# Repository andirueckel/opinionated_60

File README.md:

# opinionated_60

The opinionated_60 is a fixed-layout ANSI-based 60% mechanical keyboard PCB for *Cherry MX*-style switches with split `BACKSPACE`, split `RIGHT_SHIFT`, and 7u `SPACE` bar; there’s **no** option for a stepped `CAPS_LOCK` key.

The opinionated_60 is a rather modified, stripped-down, cleaned-up, and re-wired revision of the [Plain60 MKD Edition](https://github.com/manzel/plain60-mkd-edition) (ANSI version) by [manzel](https://github.com/manzel), which itself is a modified version of the [Plain60 Flex Edition](https://github.com/evyd13/plain60-flex-edition) (rev2.2) by [evyd13](https://github.com/evyd13).

The PCB design and schematics were created in [KiCad 8.0.2](https://www.kicad.org/blog/2024/04/KiCad-8.0.2-Release/).

## Features

  - Fits the SINGAKBD × TGR Unikorn and the HAYTCO CAKE60! <3
  - QMK and Vial support via the respective [firmware](/firmware)
  - No LEDs, no RGB, and no underglow!
  - *n*-key rollover (NKRO)

Also fits most universal 60% cases (Mekanisk Klippe & Fjell, KBDfans Tofu, etc.), where *fits* means *Unikorn*-style *gummy o-ring friction fit*, not traditional *tray mount* as there’s **no** holes for screws! Consider universal 60% case support experimental, and please do your research regarding your specific (use) case.

## Specifications

  - ATmega32U4-AU microcontroller
  - USB 2.0 Type-C connector *(default)*, and/or
  - JST connector for unified daughterboard *(optional)*
  - ESD protection chip and fuse to protect the PCB
  - ISP pin holes for flashing [QMK](https://github.com/qmk/qmk_firmware) and [Vial](https://github.com/vial-kb/vial-qmk) firmware
  - AST1109MLTRQ audio indicator (piezo buzzer/speaker) *(optional)*

## Layout

The 7u bottom row can be configured as *blockerless*, *WKL (winkeyless)*, or *HHKB*-style.

## Plate

The plate drawings were created in KiCad’s PCB design tool and could be manufactured as “PCB” from e.g. aluminum base material or regular FR-4 in any color. CNC-machining the plate has not been attempted, yet.

## Production

PCB and plate production files for can be found in the [Gerber](/hardware/Gerber) directory.

The production files were generated via [JLCKicadTools](https://github.com/matthewlai/JLCKicadTools).

## DISCLAIMER

Absolutely no guarantee for anything.

Use at your own risk!

## LICENSE

Creative Commons Attribution Share Alike 4.0 International (CC-BY-SA-4.0)

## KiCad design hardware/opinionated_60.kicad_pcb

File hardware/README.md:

# opinionated_60

The [opinionated_60](/) is a fixed-layout ANSI-based 60% mechanical keyboard PCB for *Cherry MX*-style switches with split `BACKSPACE`, split `RIGHT_SHIFT`, and 7u `SPACE` bar; there’s **no** option for a stepped `CAPS_LOCK` key.

The opinionated_60 is a rather modified, stripped-down, cleaned-up, and re-wired revision of the [Plain60 MKD Edition](https://github.com/manzel/plain60-mkd-edition) (ANSI version) by [manzel](https://github.com/manzel), which itself is a modified version of the [Plain60 Flex Edition](https://github.com/evyd13/plain60-flex-edition) (rev2.2) by [evyd13](https://github.com/evyd13).

The PCB design and schematics were created in [KiCad 8.0.2](https://www.kicad.org/blog/2024/04/KiCad-8.0.2-Release/).

## Features

  - Fits the SINGAKBD × TGR Unikorn and the HAYTCO CAKE60! <3
  - QMK and Vial support via the respective [firmware](/firmware)
  - No LEDs, no RGB, and no underglow!
  - *n*-key rollover (NKRO)

Also fits most universal 60% cases (Mekanisk Klippe & Fjell, KBDfans Tofu, etc.), where *fits* means *Unikorn*-style *gummy o-ring friction fit*, not traditional *tray mount* as there’s **no** holes for screws! Consider universal 60% case support experimental, and please do your research regarding your specific (use) case.

## Specifications

  - ATmega32U4-AU microcontroller
  - USB 2.0 Type-C connector *(default)*, and/or
  - JST connector for unified daughterboard *(optional)*
  - ESD protection chip and fuse to protect the PCB
  - ISP pin holes for flashing [QMK](https://github.com/qmk/qmk_firmware) and [Vial](https://github.com/vial-kb/vial-qmk) firmware
  - AST1109MLTRQ audio indicator (piezo buzzer/speaker) *(optional)*

## Layout

The 7u bottom row can be configured as *blockerless*, *WKL (winkeyless)*, or *HHKB*-style.

## Plate

The plate drawings were created in KiCad’s PCB design tool and could be manufactured as “PCB” from e.g. aluminum base material or regular FR-4 in any color. CNC-machining the plate has not been attempted, yet.

## Production

PCB and plate production files for can be found in the [Gerber](/hardware/Gerber) directory.

The production files were generated via [JLCKicadTools](https://github.com/matthewlai/JLCKicadTools).

## DISCLAIMER

Absolutely no guarantee for anything.

Use at your own risk!

## LICENSE

Creative Commons Attribution Share Alike 4.0 International (CC-BY-SA-4.0)

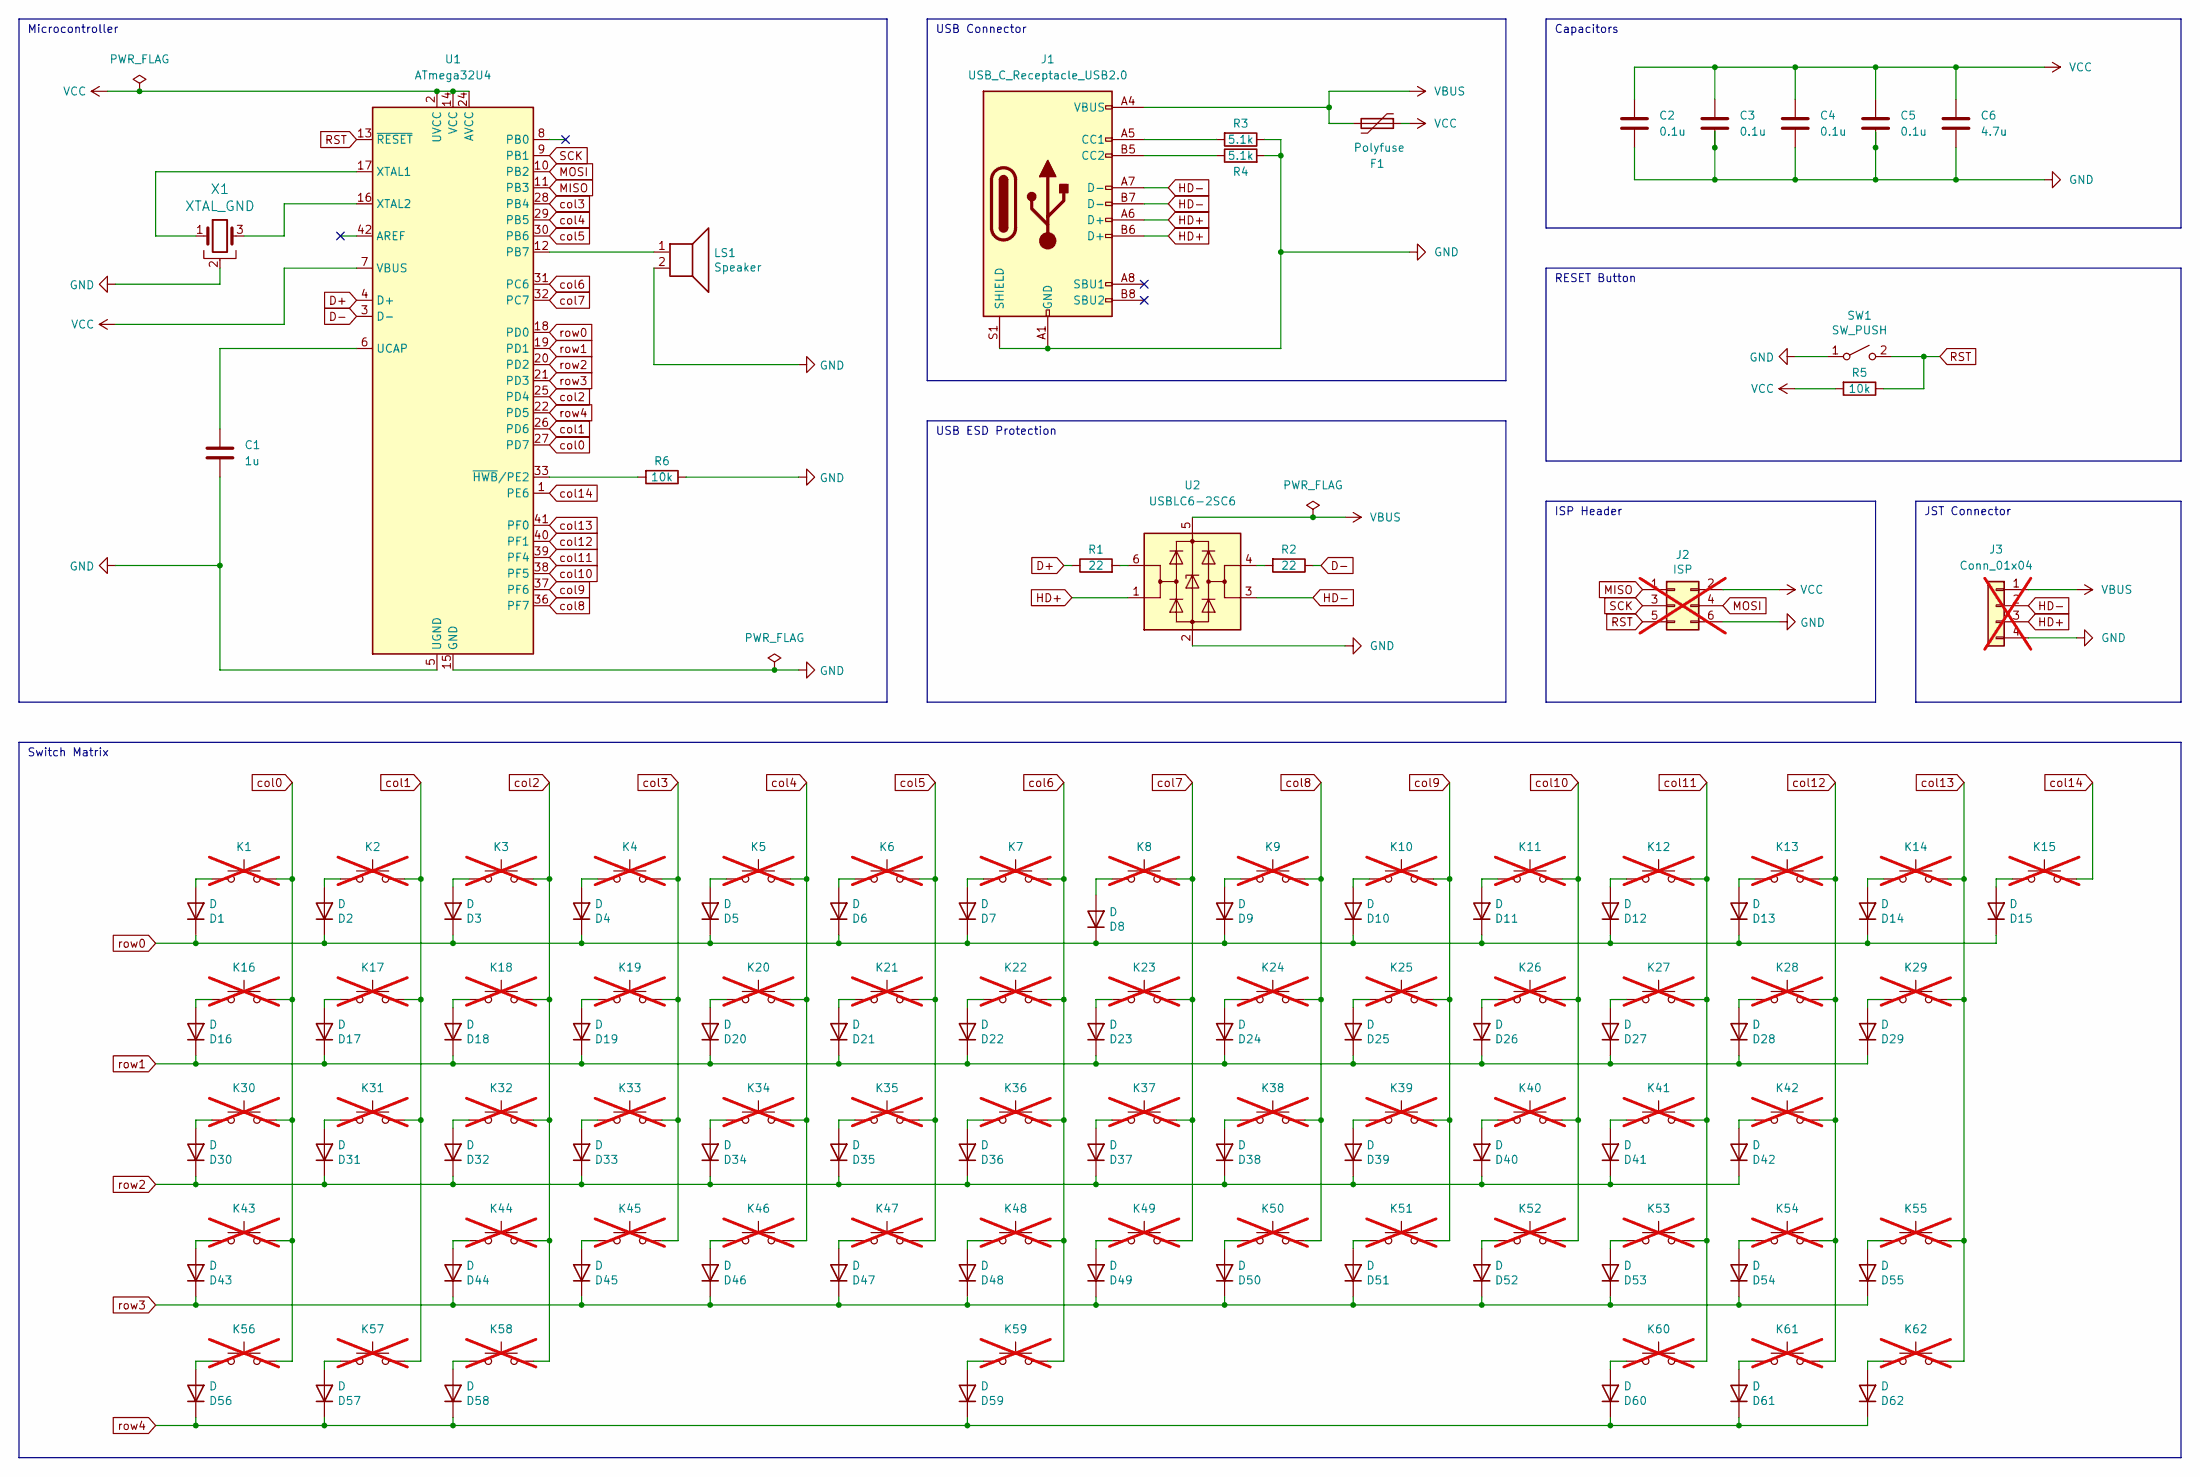
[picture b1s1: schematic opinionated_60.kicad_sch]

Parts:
C1: 1u; C_0805_2012Metric; LCSC part number C28323
C2, C3, C4, C5: 0.1u; C_0805_2012Metric; LCSC part number C49678
C6: 4.7u; C_0805_2012Metric; LCSC part number C1779
D1, D2, D3, D4, D5, D6, D7, D8, D9, D10, D11, D12, D13, D14, D15, D16, D17, D18, D19, D20, D21, D22, D23, D24, D25, D26, D27, D28, D29, D30, D31, D32, D33, D34, D35, D36, D37, D38, D39, D40, D41, D42, D43, D44, D45, D46, D47, D48, D49, D50, D51, D52, D53, D54, D55, D56, D57, D58, D59, D60, D61, D62: D; D_SOD-123; LCSC part number C2099
F1: Polyfuse; Fuse_0805_2012Metric; LCSC part number C261942
J1: USB_C_Receptacle_USB2.0; USB_C_Receptacle_HRO_TYPE-C-31-M-12; LCSC part number C165948
J2: ISP; PinHeader_2x03_P2.54mm_Vertical; not fitted
J3: Conn_01x04; JST_SH_SM04B-SRSS-TB_1x04-1MP_P1.00mm_Horizontal; LCSC part number C160404; not fitted
K1, K2, K3, K4, K5, K6, K7, K8, K9, K10, K11, K12, K13, K14, K15, K17, K18, K19, K20, K21, K22, K23, K24, K25, K26, K27, K28, K31, K32, K33, K34, K35, K36, K37, K38, K39, K40, K41, K44, K45, K46, K47, K48, K49, K50, K51, K52, K53, K55, K57, K61: SW_KEY; SW_Cherry_MX_1.00u_PCB; not fitted
K16, K29, K56, K58, K60, K62: SW_KEY; SW_Cherry_MX_1.50u_PCB; not fitted
K30, K54: SW_KEY; SW_Cherry_MX_1.75u_PCB; not fitted
K42, K43: SW_KEY; SW_Cherry_MX_2.25u_PCB; not fitted
K59: SW_KEY; SW_Cherry_MX_7.00u_PCB; not fitted
LS1: Speaker; Buzzer_Mallory_AST1109MLTRQ; LCSC part number C391036
R1, R2: 22; R_0805_2012Metric; LCSC part number C17561
R3, R4: 5.1k; R_0805_2012Metric; LCSC part number C27834
R5, R6: 10k; R_0805_2012Metric; LCSC part number C17414
SW1: SW_PUSH; SW_SPST_TL3342; LCSC part number C92584
U1: ATmega32U4; TQFP-44_10x10mm_P0.8mm; LCSC part number C44854
U2: USBLC6-2SC6; SOT-23-6; LCSC part number C7519
X1: XTAL_GND; Resonator_SMD_Murata_CSTxExxV-3Pin_3.0x1.1mm; LCSC part number C783275

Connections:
D+: R1.1, U1.4 (D+)
D-: R2.1, U1.3 (D-)
GND: C1.2, C2.2, C3.2, C4.2, C5.2, C6.2, J1.A1 (GND), J1.A12 (GND), J1.B1 (GND), J1.B12 (GND), J1.S1 (SHIELD), J2.6, J3.4, LS1.2, R3.1, R4.2, R6.1, SW1.1 (A), U1.5 (UGND), U1.15 (GND), U1.23 (GND), U1.35 (GND), U1.43 (GND), U2.2 (GND), X1.2
HD+: J1.A6 (D+), J1.B6 (D+), J3.3, U2.1 (I/O1)
HD-: J1.A7 (D-), J1.B7 (D-), J3.2, U2.3 (I/O2)
MISO: J2.1, U1.11 (PB3)
MOSI: J2.4, U1.10 (PB2)
unnamed: D1.2 (A), K1.2
unnamed: D2.2 (A), K2.2
unnamed: D3.2 (A), K3.2
unnamed: D4.2 (A), K4.2
unnamed: D5.2 (A), K5.2
unnamed: D6.2 (A), K6.2
unnamed: D7.2 (A), K7.2
unnamed: D8.2 (A), K8.2
unnamed: D9.2 (A), K9.2
unnamed: D10.2 (A), K10.2
unnamed: D11.2 (A), K11.2
unnamed: D12.2 (A), K12.2
unnamed: D13.2 (A), K13.2
unnamed: D14.2 (A), K14.2
unnamed: D15.2 (A), K15.2
unnamed: D16.2 (A), K16.2
unnamed: D17.2 (A), K17.2
unnamed: D18.2 (A), K18.2
unnamed: D19.2 (A), K19.2
unnamed: D20.2 (A), K20.2
unnamed: D21.2 (A), K21.2
unnamed: D22.2 (A), K22.2
unnamed: D23.2 (A), K23.2
unnamed: D24.2 (A), K24.2
unnamed: D25.2 (A), K25.2
unnamed: D26.2 (A), K26.2
unnamed: D27.2 (A), K27.2
unnamed: D28.2 (A), K28.2
unnamed: D29.2 (A), K29.2
unnamed: D30.2 (A), K30.2
unnamed: D31.2 (A), K31.2
unnamed: D32.2 (A), K32.2
unnamed: D33.2 (A), K33.2
unnamed: D34.2 (A), K34.2
unnamed: D35.2 (A), K35.2
unnamed: D36.2 (A), K36.2
unnamed: D37.2 (A), K37.2
unnamed: D38.2 (A), K38.2
unnamed: D39.2 (A), K39.2
unnamed: D40.2 (A), K40.2
unnamed: D41.2 (A), K41.2
unnamed: D42.2 (A), K42.2
unnamed: D43.2 (A), K43.2
unnamed: D44.2 (A), K44.2
unnamed: D45.2 (A), K45.2
unnamed: D46.2 (A), K46.2
unnamed: D47.2 (A), K47.2
unnamed: D48.2 (A), K48.2
unnamed: D49.2 (A), K49.2
unnamed: D50.2 (A), K50.2
unnamed: D51.2 (A), K51.2
unnamed: D52.2 (A), K52.2
unnamed: D53.2 (A), K53.2
unnamed: D54.2 (A), K54.2
unnamed: D55.2 (A), K55.2
unnamed: D56.2 (A), K56.2
unnamed: D57.2 (A), K57.2
unnamed: D58.2 (A), K58.2
unnamed: D59.2 (A), K59.2
unnamed: D60.2 (A), K60.2
unnamed: D61.2 (A), K61.2
unnamed: D62.2 (A), K62.2
unnamed: J1.A5 (CC1), R3.2
unnamed: J1.B5 (CC2), R4.1
unnamed: R1.2, U2.6 (I/O1)
unnamed: R2.2, U2.4 (I/O2)
unnamed: LS1.1, U1.12 (PB7)
unnamed: C1.1, U1.6 (UCAP)
unnamed: U1.17 (XTAL1), X1.1
unnamed: U1.16 (XTAL2), X1.3
unnamed: R6.2, U1.33 (~HWB/PE2)
RST: J2.5, R5.1, SW1.2 (B), U1.13 (~RESET)
SCK: J2.3, U1.9 (PB1)
VBUS: F1.2, J1.A4 (VBUS), J1.A9 (VBUS), J1.B4 (VBUS), J1.B9 (VBUS), J3.1, U2.5 (VBUS)
VCC: C2.1, C3.1, C4.1, C5.1, C6.1, F1.1, J2.2, R5.2, U1.2 (UVCC), U1.7 (VBUS), U1.14 (VCC), U1.24 (AVCC), U1.34 (VCC), U1.44 (AVCC)
col0: K1.1, K16.1, K30.1, K43.1, K56.1, U1.27 (PD7)
col1: K2.1, K17.1, K31.1, K57.1, U1.26 (PD6)
col2: K3.1, K18.1, K32.1, K44.1, K58.1, U1.25 (PD4)
col3: K4.1, K19.1, K33.1, K45.1, U1.28 (PB4)
col4: K5.1, K20.1, K34.1, K46.1, U1.29 (PB5)
col5: K6.1, K21.1, K35.1, K47.1, U1.30 (PB6)
col6: K7.1, K22.1, K36.1, K48.1, K59.1, U1.31 (PC6)
col7: K8.1, K23.1, K37.1, K49.1, U1.32 (PC7)
col8: K9.1, K24.1, K38.1, K50.1, U1.36 (PF7)
col9: K10.1, K25.1, K39.1, K51.1, U1.37 (PF6)
col10: K11.1, K26.1, K40.1, K52.1, U1.38 (PF5)
col11: K12.1, K27.1, K41.1, K53.1, K60.1, U1.39 (PF4)
col12: K13.1, K28.1, K42.1, K54.1, K61.1, U1.40 (PF1)
col13: K14.1, K29.1, K55.1, K62.1, U1.41 (PF0)
col14: K15.1, U1.1 (PE6)
row0: D1.1 (K), D2.1 (K), D3.1 (K), D4.1 (K), D5.1 (K), D6.1 (K), D7.1 (K), D8.1 (K), D9.1 (K), D10.1 (K), D11.1 (K), D12.1 (K), D13.1 (K), D14.1 (K), D15.1 (K), U1.18 (PD0)
row1: D16.1 (K), D17.1 (K), D18.1 (K), D19.1 (K), D20.1 (K), D21.1 (K), D22.1 (K), D23.1 (K), D24.1 (K), D25.1 (K), D26.1 (K), D27.1 (K), D28.1 (K), D29.1 (K), U1.19 (PD1)
row2: D30.1 (K), D31.1 (K), D32.1 (K), D33.1 (K), D34.1 (K), D35.1 (K), D36.1 (K), D37.1 (K), D38.1 (K), D39.1 (K), D40.1 (K), D41.1 (K), D42.1 (K), U1.20 (PD2)
row3: D43.1 (K), D44.1 (K), D45.1 (K), D46.1 (K), D47.1 (K), D48.1 (K), D49.1 (K), D50.1 (K), D51.1 (K), D52.1 (K), D53.1 (K), D54.1 (K), D55.1 (K), U1.21 (PD3)
row4: D56.1 (K), D57.1 (K), D58.1 (K), D59.1 (K), D60.1 (K), D61.1 (K), D62.1 (K), U1.22 (PD5)

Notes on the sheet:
USB ESD Protection
RESET Button
JST Connector
Switch Matrix
Microcontroller
Capacitors
ISP Header
USB Connector

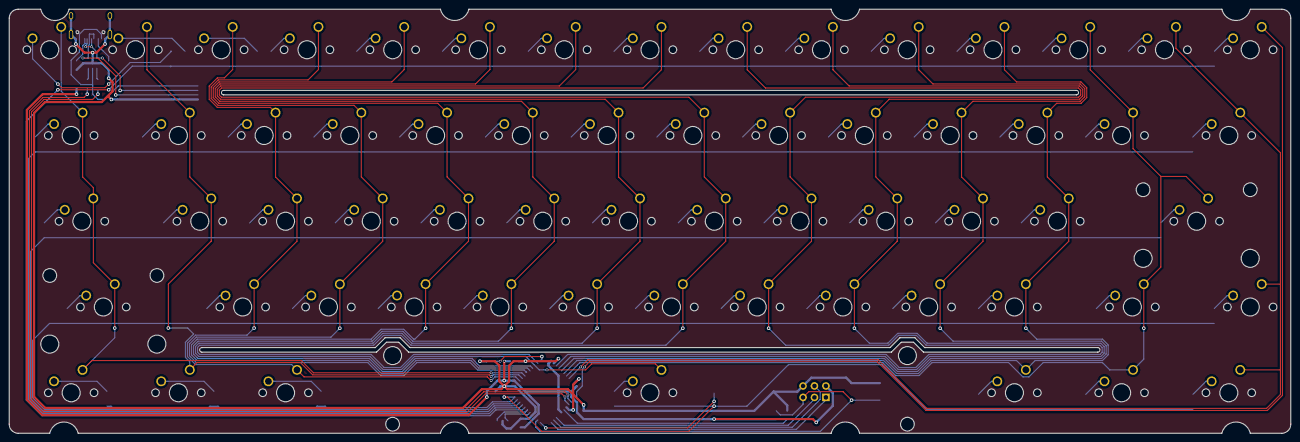
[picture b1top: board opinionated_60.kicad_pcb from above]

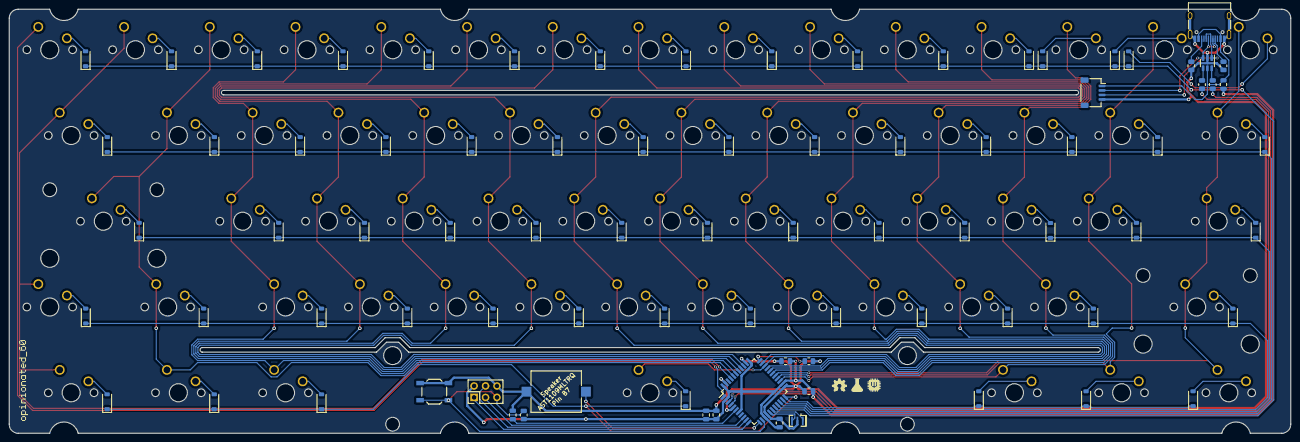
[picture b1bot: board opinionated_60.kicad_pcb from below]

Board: 2 copper layers, 284.7 x 94.2 mm, 149 parts (87 on the bottom side), 102 nets.

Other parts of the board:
LOGO_OSHW: LOGO; LOGO_OSHW
LOGO_QMK: LOGO; LOGO_QMK
LOGO_Vial: LOGO; LOGO_Vial
LOGO_opinionated_60: LOGO; LOGO_opinionated_60
